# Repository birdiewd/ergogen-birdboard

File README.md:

# birdboard v4.6

A split keyboard designed with [Ergogen](https://ergogen.xyz). The art on the case and plate,
and the keycap legends, are UV printed. It's handwired, like the
[Scotto44](https://scottokeebs.com/blogs/keyboards/scotto44): there is no PCB. The Gateron
low-profile switches clip into a 3D-printed plate that covers just the keys. The 1N4148 diodes
and the 18 AWG solid copper rows and columns are soldered straight onto the switch pins. Each
half has two pods at the top of its case. The RP2040-Zero sits in the outer one, and its USB-C
port is the connection to the computer. A USB-C breakout sits in the inner one, as the link to
the other half. Both ports come out of the top wall, and the plate covers both pods.

## Setup

```bash
pnpm install
```

## Generating the STLs

The printable STLs are kept in the repo in `stl/`:

| File | Part |
| --- | --- |
| `keyboard_case.stl`, `keyboard_case_right.stl` | cases, with the module seats and standoffs, and a 0.8 mm chamfer round the bottom edge. A lip runs round the inside of the wall for the plate's edge to rest on: its top is level with the plate's underside, `lip_w` (1.2 mm) wide, with a 45° underside so it prints without supports, and it stops either side of each USB opening, with no lip across it. Each standoff is 5 mm across under the plate and flares out at 10° a side to 6.9 mm on the floor (`standoff_*`), trimmed where it would reach into a module's pocket. Its M2 heat-set insert hole is 3.2 mm across at the top and narrows at 10° a side to 2.2 mm, then runs straight down to the floor (`insert_*` in config.yaml) |
| `switchplate.stl`, `switchplate_right.stl` | switch plates (they also cover the pods) |

The case and plate print in one colour. The art on them is UV printed afterwards.

## The art, UV printed

Seen from below, each case reads as a cartoon moose head, drawn in one colour in
[art/moose.js](art/moose.js):
- **Head:** a line just inside the case edge, following it round the key area.
- **Antlers:** small blocky antlers with three prongs each, in the two pods.
- **Face:** a simple line face on the thumb-cluster muzzle.

The word "moose" is also hand-lettered on top of each switch plate, in [art/text.js](art/text.js).
It sits in the band of plate below the thumb cluster, which still shows with the keycaps on,
and runs parallel to the bottom edge. It reads left to right on both halves.

Both are printed on the eufyMake E1, like the keycap legends. `npm run stl` writes the print
files to `art/print/`:
- `print_case_left.svg`, `print_case_right.svg`: the moose, as seen looking at the case's
  underside.
- `print_plate_left.svg`, `print_plate_right.svg`: the word, as seen looking down on the plate.

Each is true size, and the drawing is exactly the part's outline's bounding box (the case
169.8 × 105.9 mm, the plate 165.7 × 101.8 mm). The art is filled shapes in a cream colour,
with no strokes and nothing else in the file.

1. Put the case upside down on the E1's bed, floor up. For the plate, put it top up.
2. In eufyMake Studio, import that part's print file. Line the drawing's edges up with the
   part's outermost edges in the camera view, and size it to the part if it isn't already.
3. Use a white underlay on a dark case or plate, so the cream stays bright.
4. Print, then do the other half with its own file.

`npm run build` also writes previews, the art drawn on its part: `output/art/moose_left.svg`
and `moose_right.svg` (seen from below), and `output/art/text_left.svg` and `text_right.svg`
(seen from above, with the keycaps shaded, so you can see the word stays clear of them).

## Keycaps and legends

The keycaps are our own: low profile, Chicago Steno style, for the KS-33's MX-style cross stem.
Their legends are UV printed on a eufyMake E1. Everything is generated from
[config.yaml](config.yaml) (the `cap_*` and `holder_*` settings) and the keymap plan,
[keymap/legends.json](keymap/legends.json).

### Chicago-style caps, printed on their side

Two side profiles traced from a picture run the full width of the cap. Each cap is one
piece, with the stem post joined under its top and its end level with the bottom of the skirt,
so the post rides on the switch's slider and the skirt can't reach the plate at bottom-out.

| File | Part |
| --- | --- |
| `stl/keycap_cs_top_1u.stl` | top row: 8.55 mm at its peak, 7.6 mm near the back, 4.3 mm near the front. Turned round, tall side to the front, it's the bottom row's cap too (print 24) |
| `stl/keycap_cs_home_1u.stl` | home row: 4.74 mm in the middle, 3.5 mm near the front and back, the same both ways. Also the 1u thumb keys (print 20) |
| `stl/keycap_cs_home_1u_homing.stl` | home row with a homing bump, for F and J: a rounded bar 5 mm long standing `cap_cs_homing_bump` (0.6 mm) proud of the face, 2.5 mm from the front edge (print 2) |
| `stl/keycap_cs_thumb_1_5u.stl` | 1.5u inner thumb key, in the home row's profile (print 2) |
| `stl/keycap_holder.stl` | holds one half's 24 caps, top up, on the E1's bed |

**The profiles:** the side views are in [art/cs_profiles.png](art/cs_profiles.png), with
[art/cs_profiles_zoom.png](art/cs_profiles_zoom.png), a sharper screenshot of their tops.
`node art/trace-profile.js` traces them into `art/cs_profiles.json` and draws
[art/cs_profiles.svg](art/cs_profiles.svg) to check them by:
- **Scale:** each shape's width at its base is the cap's 18 mm depth, and its base is the
  bottom of the skirt.
- **Smoothing:** the two pictures' traces are averaged and smoothed. The result stays
  within 0.1 mm of the traces, and its control points are crowded into the corners.
- **Home row:** its profile is averaged with its own mirror image, so it's the same front
  and back.

**The cap:** the left and right faces have a draft of `cap_draft` over the cap's height, and the top's
left and right edges are chamfered `cap_cs_edge` (0.6 mm). The top has a shallow dish:
`cap_cs_dish` (0.8 mm) deep in the middle, easing to nothing at the left and right edges
and at the front and back, on top of the profile (the heights in the table above are the
profile's, along the edges; set `cap_cs_dish` to 0 for a flat top). Inside, a hollow keeps
`cap_top_t` (1.2 mm) under the curved top, measured from the dish's lowest line, and is no
higher than the 3.3 mm skirt, so it's lower near a rounded edge and under the dish. The top over the stem is 1.24 mm thick on the home cap.
The 1.5u thumb cap's top isn't level across its width. It follows the curve in
`art/cs_thumb_curve.json`, which was traced from a sketch: a long gentle slope up to its plain
end, and a sweep down to the bottom at its other end, with no chamfer or end face there. At
the middle of the profile the top is 4.7 mm high at the plain end, 4.0 mm over the stem and
2.5 mm 2.4 mm from the swept end. It has no dish. The hollow follows the curve, so the top is
`cap_top_t` thick all the way down, and the hollow stops with a straight drop where its
ceiling gets down to 0.4 mm. The swept end's two corners are rounded `cap_cs_thumb_corner_r`
(3 mm) seen from above. Over the socket the top is about 0.9 mm thick. The cap still
prints on its plain end. The swept end goes at the key's lower end: on the left half the cap
is turned round, and on the right half it isn't. Its side profile is the same both ways, so
only that end shows which way it goes. To change the curve, edit the json: each point is the
height, as a share of the profile's, at a place from the swept end (0) to the plain end (1).

**Printing:** the caps print lying on their left face, and the STLs are already turned that
way. So every layer is the profile, and the curve comes out smooth whatever its shape.
Lying like that, the hollow's right side is a ceiling: a flat overhang, since both side
walls are `cap_wall` thick and drafted alike, so it may need supports.
The stem post runs sideways, 3.6 mm out from the top with nothing under it. Its round
underside is an overhang, so if it sags on your printer, add a support under the post in the
slicer.

**Supports:** each cap also has a `_supported` STL (`keycap_cs_*_supported.stl`): the cap with
a scaffold beside it, a separate solid that touches the cap nowhere. A thin round-ended
baseplate lies on the bed next to the cap's open end, with two leaning struts from it into the
open end. Each strut is round, `sup_foot_w` (5 mm) wide where it stands on the bed, and tapers
evenly to `sup_arm_w` (1.6 mm) at the top, where it splits into a fan of three tines. The
tines are `sup_tine_root_w` (1.2 mm) wide where they split off and taper evenly to `sup_w`
(0.8 mm) at their ends, which stop `sup_gap` (0.08 mm, one layer) short of the stem post's
underside and of the hollow's ceiling, so the scaffold breaks away by hand.
The 1.5u thumb cap has only the post's strut. Its ceiling slopes, so printed upright it
overhangs past 45 degrees for only 0.5 mm, and a ceiling gets tines only if that's over
`sup_overhang_ok` (2 mm).
The build checks every part's distance to the cap and stops if one is closer than the gap.
Print the plain STL if you'd rather use the slicer's supports.

They sit in the legend holder. Put each bottom-row cap in the holder turned
round, tall side to the front, as it sits on the keyboard, so its legend prints the right way
up.

**Fit:** the cross socket's clearance is `cap_stem_tol`. It's 0.2 mm, the best fit from an
earlier fit test of 0.05 to 0.2 mm. If the stems grip too tightly or too loosely on another
printer, change it and export again.

### Planning the legends

Run `npm run view` and open http://localhost:4600/keymap (or **Keymap ↗** in the viewer):
- **Keys:** both halves are shown as they're laid out. Click a key and type its legends. Each
  legend goes in its own corner, reading clockwise from the top left:
  - **Base:** top left.
  - **Shift:** top right, in the shift colour.
  - **Raise:** bottom right, in its colour.
  - **Lower:** bottom left, in its colour.

  A key with only a base legend (space, enter, the media keys) has it in the middle instead.
  Two legends in the same row shrink together if they'd run into each other.
- **Colours:** the menu beside the base legend can draw it in the shift colour or a layer's
  colour instead, e.g. for the key that switches to that layer (the middle thumb keys are Lower
  and Raise). The **Top** menu fills the key's whole top with the shift colour or a layer's
  colour, printed under its legends.
- **Moving between keys:** Tab, Shift+Tab and Enter.
- **Faces:** the **Flat caps / Chicago caps** switch at the top picks which caps the keys are
  drawn as. With Chicago caps, each key shows the face of the cap it takes, seen from above
  (the bottom row's turned round). The face is outlined, and darker wherever it's steeper than
  `cap_cs_print_slope` (30°), because a UV-printed legend lands stretched there. Keep legends
  on the lighter part. The legends are laid out on a flat top, so this is a check, not a
  change to where they print.
- **Icons:** the icon panel searches Font Awesome Free's 1,895 icons by name and search terms.
  Click one to put it in the legend you're editing. In a legend, an icon is written as its
  name between colons, `:volume-high:`. Solid style is the default; `:regular/keyboard:` and
  `:brands/apple:` pick the others. Unicode symbols (⌘ ⌥ ⏎ and the like) still work too.
- **Layers and style:** each layer's name, colour and place on the cap (either side, or any
  corner), the cap colour, legend sizes, and the legends' padding from the edges of the cap's
  top: **Padding** sets the left-and-right (`style.side.padX`) and the top-and-bottom
  (`style.side.padY`) separately. The base and shift legends have a place menu too:
  either side, any corner, or their old spots (the middle for base, centred along the top for
  shift). The buttons at the top show one layer at a time.
- Changes save to `keymap/legends.json` on their own.

The legends are set in Segoe UI Bold, with Segoe UI Symbol for symbols. These are read from
Windows' fonts folder at build time and written into the print files as outlines, so the printer
never substitutes a font. Other TrueType fonts can be set in the plan's `style`. Symbol fonts
draw arrows and icons small and light, so symbols are drawn larger and bolder than the font has
them, centred on the letters' height: `style.symbol.scale` (1.4 times) and
`style.symbol.weight` (fattened by 0.07 mm all round).

Icons come from [Font Awesome Free](https://fontawesome.com) 6.7.2, whose fonts and icon list
are kept in [keymap/fonts/fontawesome/](keymap/fonts/fontawesome/). Its icons are licensed
under CC BY 4.0 and its fonts under the SIL OFL 1.1; see the
[licence](keymap/fonts/fontawesome/LICENSE.txt). (Version 6 is used because version 7 ships
only compressed web fonts.) An icon's size is set by `style.icons.scale`: its em square is
that many cap heights (1.3).

### Printing the legends on the E1

`npm run stl` writes the print files to `keymap/print/`:
- `print_left.svg`, `print_right.svg`: one half's legends each, at true size. The drawing is
  exactly the holder's outline, 219 × 81 mm. That fits the E1's mini flatbed (330 × 90 mm),
  and the build stops if a change to the `holder_*` settings would make it too big for it.
- `preview_left.svg`, `preview_right.svg`: the same on the holder, with each slot's key named.

1. Print the holder and the caps, then put one half's caps in the holder, top up. The 1.5u
   cap goes in the wide slot, and the cut-off corner goes top left. Lay the holder along the
   mini flatbed.
2. In eufyMake Studio, import that half's print file. Line its edges up with the holder in
   the camera view, and size it to 219 × 81 mm if it isn't already.
3. Use a white underlay if the caps are a dark colour, so the coloured legends stay bright.
4. Print, then swap in the other half's caps and do the same with its print file. The
   preview shows which key each slot's cap belongs to.

## Wiring guide

`npm run build` also draws a wiring guide for each half: `output/wiring/wiring_left.svg` and
`wiring_right.svg`. Each is seen from below, as you wire it. The matching
`output/wiring/report_*.md` files have the MCU pin map, the assembly order and the wire lengths.
Both halves use the same pin map.

## Other commands

- `npm run build`: builds Ergogen and the wiring guides into `output/`.
- `npm run view`: starts the local viewer at http://localhost:4600. It rebuilds on every edit and shows the outlines and the 3D cases. In the 3D tab, **Assembled** puts the plates on their standoffs, the right half beside the left, and a Chicago-style keycap on every key (the bottom row's turned round). The caps sit `cap_seat` (3 mm, an estimate) above the plate.

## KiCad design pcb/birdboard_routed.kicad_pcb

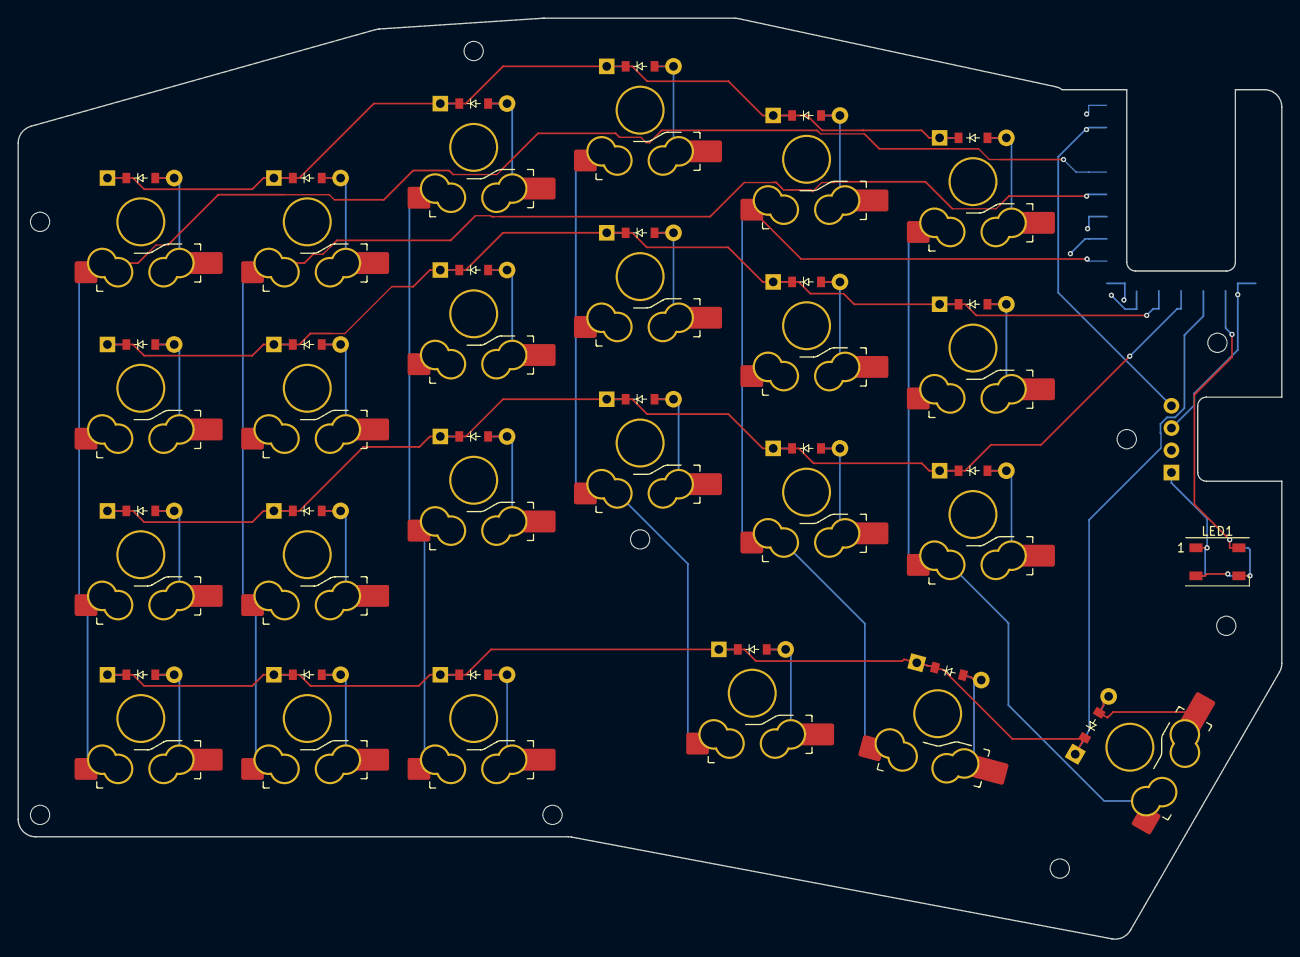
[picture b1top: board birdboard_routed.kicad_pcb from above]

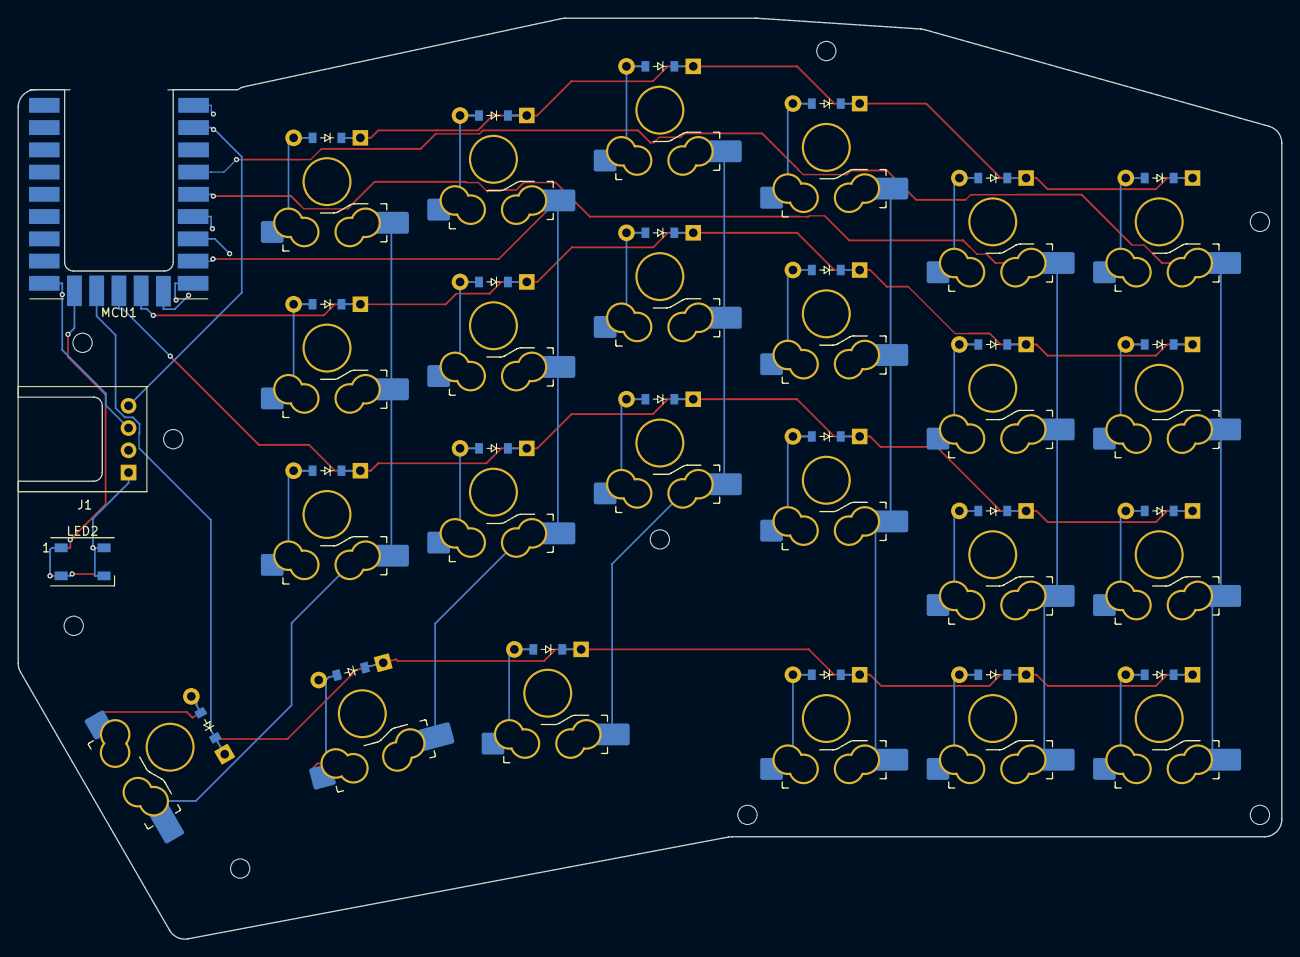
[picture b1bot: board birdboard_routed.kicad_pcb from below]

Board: 2 copper layers, 144.3 x 105.1 mm, 61 parts (27 on the bottom side), 39 nets.

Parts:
D1, D2, D3, D4, D5, D6, D7, D8, D9, D10, D11, D12, D13, D14, D15, D16, D17, D18, D19, D20, D21, D22, D23, D24: diode_k8
H1, H2, H3, H4, H5, H6, H7, H8, H9: mounting_hole
J1: usbc_breakout_4pin
LED1, LED2: led_ws2812b_5050
MCU1: mcu_rp2040_zero
S1, S2, S3, S4, S5, S6, S7, S8, S9, S10, S11, S12, S13, S14, S15, S16, S17, S18, S19, S20, S21, S22, S23, S24: switch_gateron_ks27_ks33

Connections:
5V: J1.1, LED1.1, LED2.1, MCU1.1
C0: MCU1.4, S1.1, S2.1, S3.1, S19.1
C1: MCU1.5, S4.1, S5.1, S6.1, S20.1
C2: MCU1.6, S7.1, S8.1, S9.1, S21.1
C3: MCU1.7, S10.1, S11.1, S12.1, S22.1
C4: MCU1.8, S13.1, S14.1, S15.1, S23.1
C5: MCU1.9, S16.1, S17.1, S18.1, S24.1
GND: J1.4, LED1.3, LED2.3, MCU1.2
LED: LED1.4, MCU1.23
LED_2: LED1.2, LED2.4
LINK: J1.3, MCU1.18
R0: D3.1, D6.1, D9.1, D12.1, D15.1, D18.1, MCU1.19
R1: D2.1, D5.1, D8.1, D11.1, D14.1, D17.1, MCU1.20
R2: D1.1, D4.1, D7.1, D10.1, D13.1, D16.1, MCU1.21
R3: D19.1, D20.1, D21.1, D22.1, D23.1, D24.1, MCU1.22
matrix_index_bottom: D13.2, S13.2
matrix_index_home: D14.2, S14.2
matrix_index_top: D15.2, S15.2
matrix_inner_bottom: D16.2, S16.2
matrix_inner_home: D17.2, S17.2
matrix_inner_top: D18.2, S18.2
matrix_middle_bottom: D10.2, S10.2
matrix_middle_home: D11.2, S11.2
matrix_middle_top: D12.2, S12.2
matrix_outer_bottom: D1.2, S1.2
matrix_outer_home: D2.2, S2.2
matrix_outer_top: D3.2, S3.2
matrix_pinky_bottom: D4.2, S4.2
matrix_pinky_home: D5.2, S5.2
matrix_pinky_top: D6.2, S6.2
matrix_ring_bottom: D7.2, S7.2
matrix_ring_home: D8.2, S8.2
matrix_ring_top: D9.2, S9.2
mod_outer_thumb: D19.2, S19.2
mod_pinky_thumb: D20.2, S20.2
mod_ring_thumb: D21.2, S21.2
thumbfan_fn_thumb: D23.2, S23.2
thumbfan_home_thumb: D24.2, S24.2
thumbfan_outer_thumb: D22.2, S22.2
